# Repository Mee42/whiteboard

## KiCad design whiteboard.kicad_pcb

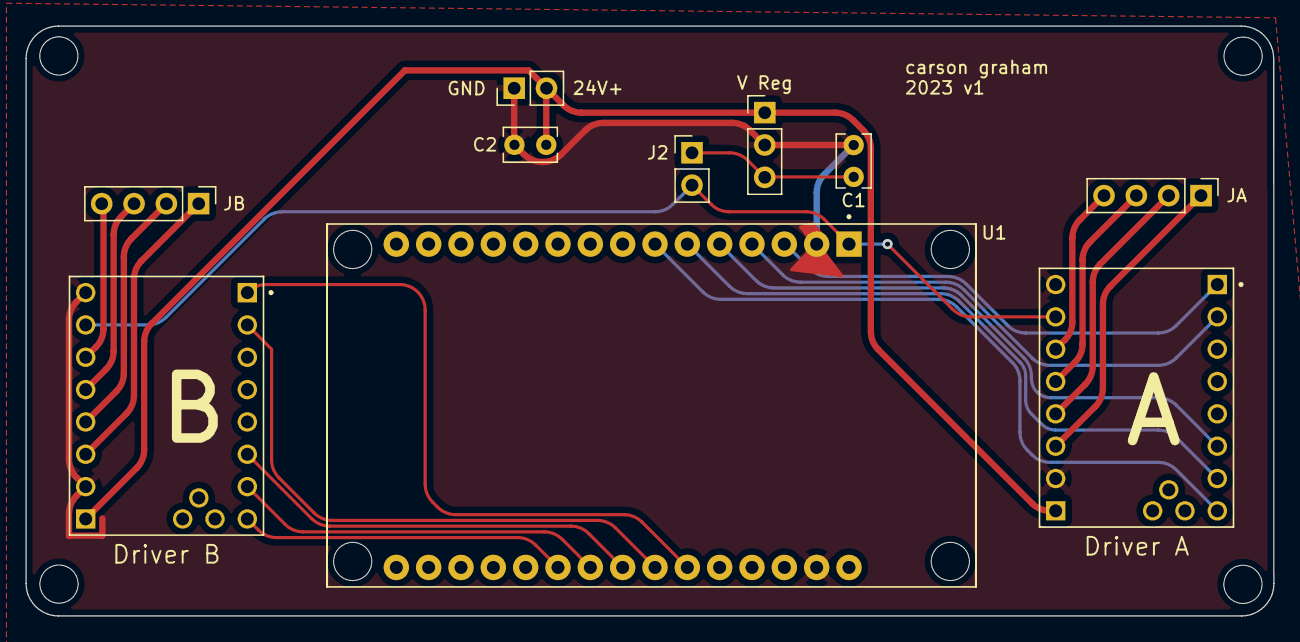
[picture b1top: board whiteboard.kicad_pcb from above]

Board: 2 copper layers, 98.0 x 46.3 mm, 10 parts (0 on the bottom side), 22 nets.

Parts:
24V+: Conn_01x02; PinHeader_1x02_P2.54mm_Vertical
C1: 10uF; C_Rect_L4.0mm_W2.5mm_P2.50mm
C2: 22uF; C_Rect_L4.0mm_W2.5mm_P2.50mm
Driver A: TMC2208_SILENTSTEPSTICK; MODULE_TMC2208_SILENTSTEPSTICK
Driver B: TMC2208_SILENTSTEPSTICK; MODULE_TMC2208_SILENTSTEPSTICK
J2: Jumper_2_Open; PinHeader_1x02_P2.54mm_Vertical
JA: Conn_01x04; PinHeader_1x04_P2.54mm_Vertical
JB: Conn_01x04; PinHeader_1x04_P2.54mm_Vertical
U1: ESP32-DEVKIT-V1; MODULE_ESP32_DEVKIT_V1
V Reg: Conn_01x03; PinHeader_1x03_P2.54mm_Vertical

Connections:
+3V3: Driver A.JP2_7 (VIO), Driver B.JP2_7 (VIO), J2.2 (B), U1.1 (3V3)
+24V: 24V+.2, C2.1, Driver A.JP2_1 (VM), Driver B.JP2_1 (VM), V Reg.1
DIR_A: Driver A.JP1_1 (DIR), U1.3 (D15)
DIR_B: Driver B.JP1_1 (DIR), U1.25 (D27)
EN_A: Driver A.JP1_8 (EN), U1.7 (TX2)
EN_B: Driver B.JP1_8 (EN), U1.21 (D32)
GND: 24V+.1, C1.2, C2.2, Driver A.JP2_2 (GND), Driver A.JP2_8 (GND), Driver B.JP2_2 (GND), Driver B.JP2_8 (GND), U1.2 (GND), U1.29 (GND), V Reg.2
MS1_A: Driver A.JP1_7 (MS1), U1.6 (RX2)
MS1_B: Driver B.JP1_7 (MS1), U1.22 (D33)
MS2_A: Driver A.JP1_6 (MS2), U1.5 (D4)
MS2_B: Driver B.JP1_6 (MS2), U1.23 (D25)
unnamed: Driver B.JP2_3 (OA2), JB.1
unnamed: C1.1, J2.1 (A), V Reg.3
unnamed: Driver A.JP2_3 (OA2), JA.1
unnamed: Driver A.JP2_4 (OA1), JA.2
unnamed: Driver A.JP2_5 (OB1), JA.3
unnamed: Driver A.JP2_6 (OB2), JA.4
unnamed: Driver B.JP2_4 (OA1), JB.2
unnamed: Driver B.JP2_5 (OB1), JB.3
unnamed: Driver B.JP2_6 (OB2), JB.4
STEP_A: Driver A.JP1_2 (STEP), U1.4 (D2)
STEP_B: Driver B.JP1_2 (STEP), U1.24 (D26)

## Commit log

2022-04-20 started cadding some parts for practice
2022-04-20 actually saved files
2022-08-17 inital commit
2022-08-18 Draws catgit add .!
2022-09-20 http server testing
2022-09-22 Fucking works!
2022-09-22 removed old c driver
2022-10-07 wpi-wireless worksgit add .!
2022-10-07 wifi works and code is better
2022-10-08 SHIT WORKS
2022-10-08 fucking works lmao
2022-10-12 spinning works!
2022-10-12 iremoved cache lmao
2022-10-12 inital comit
2023-01-15 shit works!!
2023-01-16 works a bit better :)
2023-01-16 yknow it kinda works
2023-01-27 fucking works! can go to a specific spot with great accuracy
2023-01-27 okay so the threads are fucky. Figure out how to post status, move the steppers, and not block the entire processor at the same time :)
2023-02-12 shit actually works! spintask and http run sequencially
2023-02-12 v1 pcb
